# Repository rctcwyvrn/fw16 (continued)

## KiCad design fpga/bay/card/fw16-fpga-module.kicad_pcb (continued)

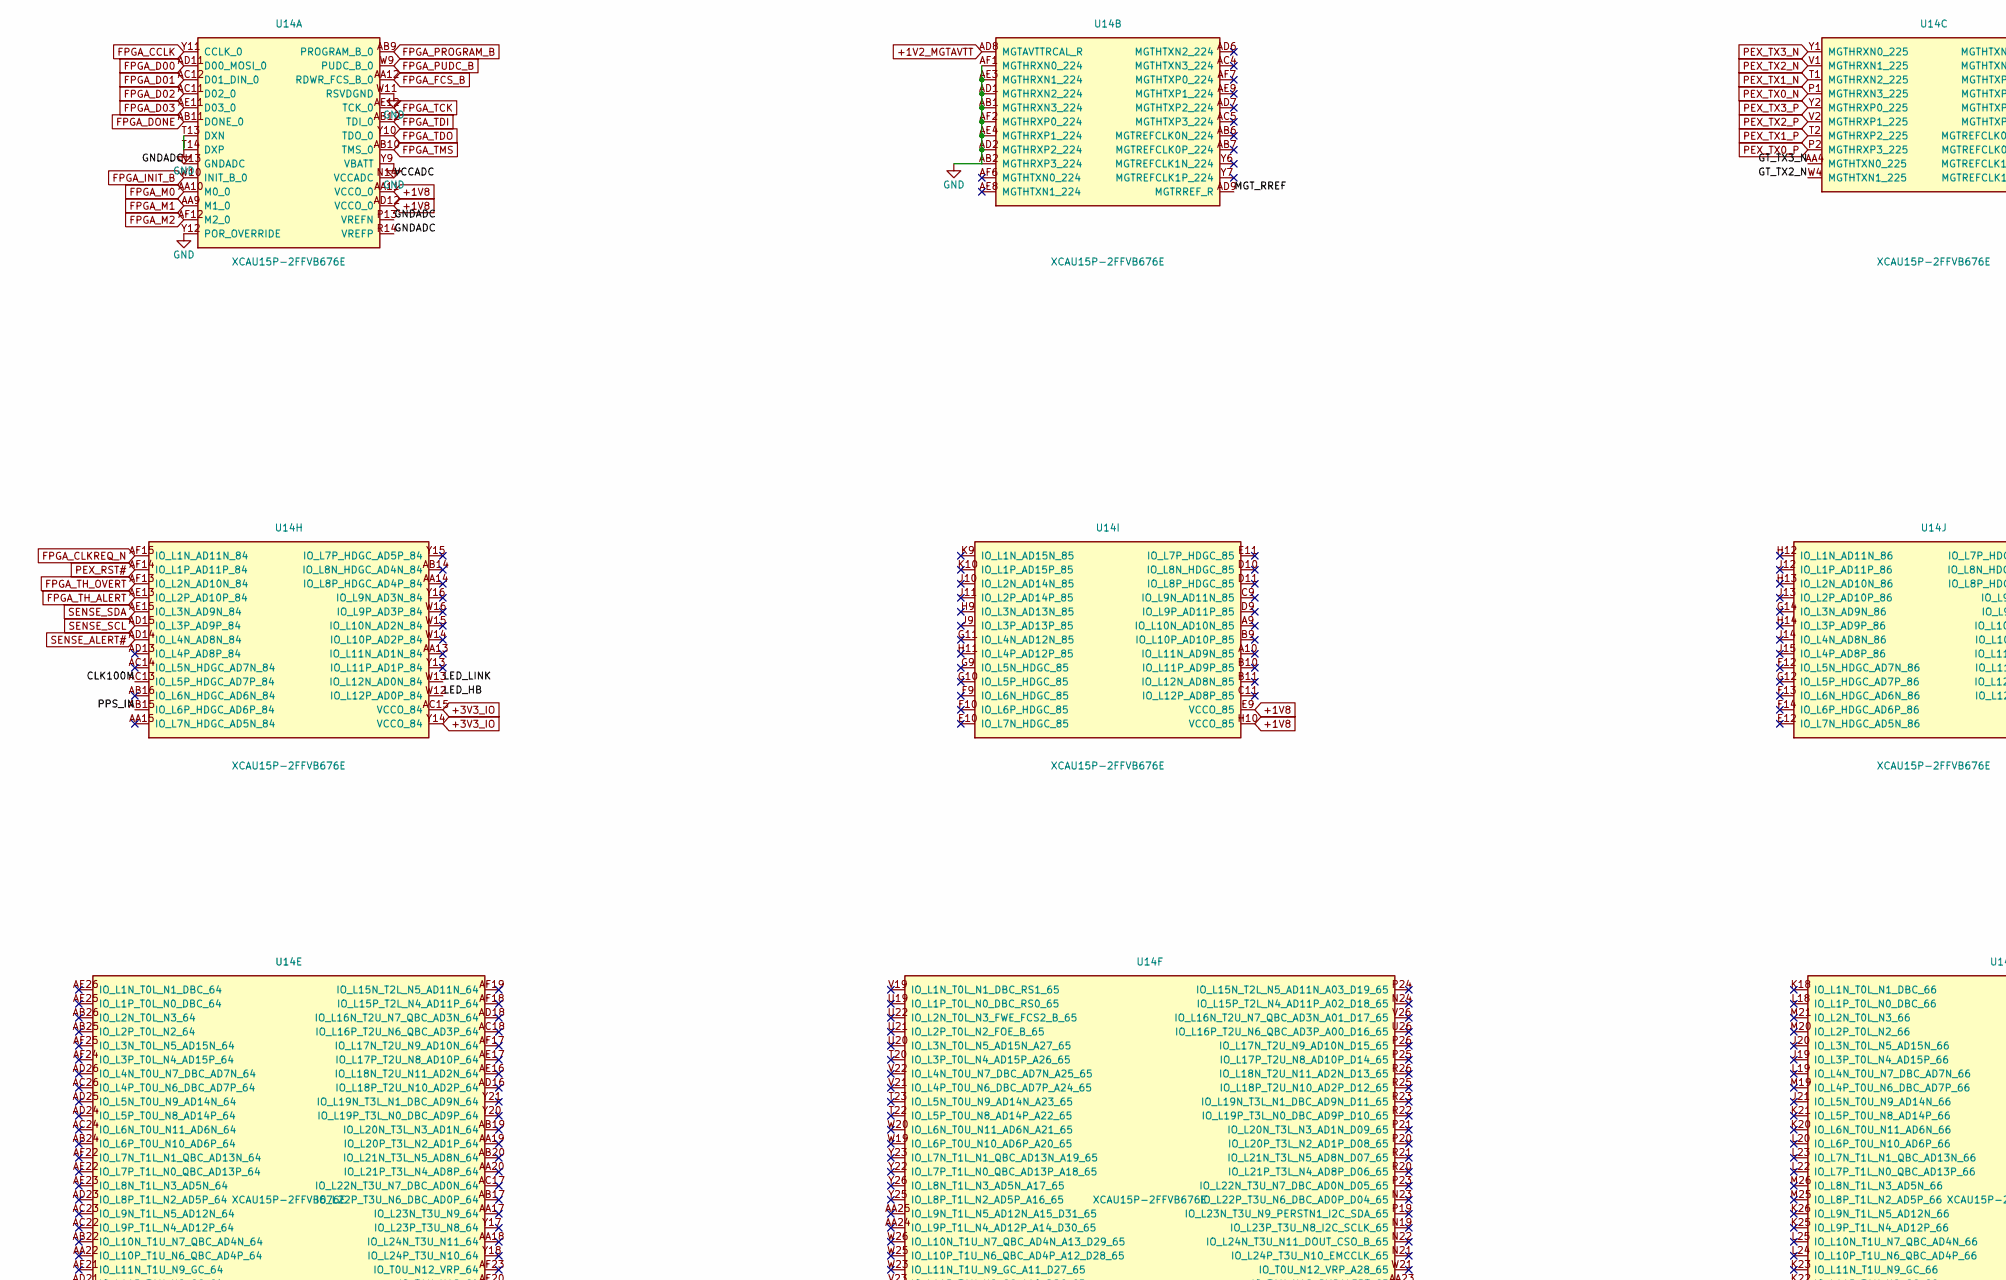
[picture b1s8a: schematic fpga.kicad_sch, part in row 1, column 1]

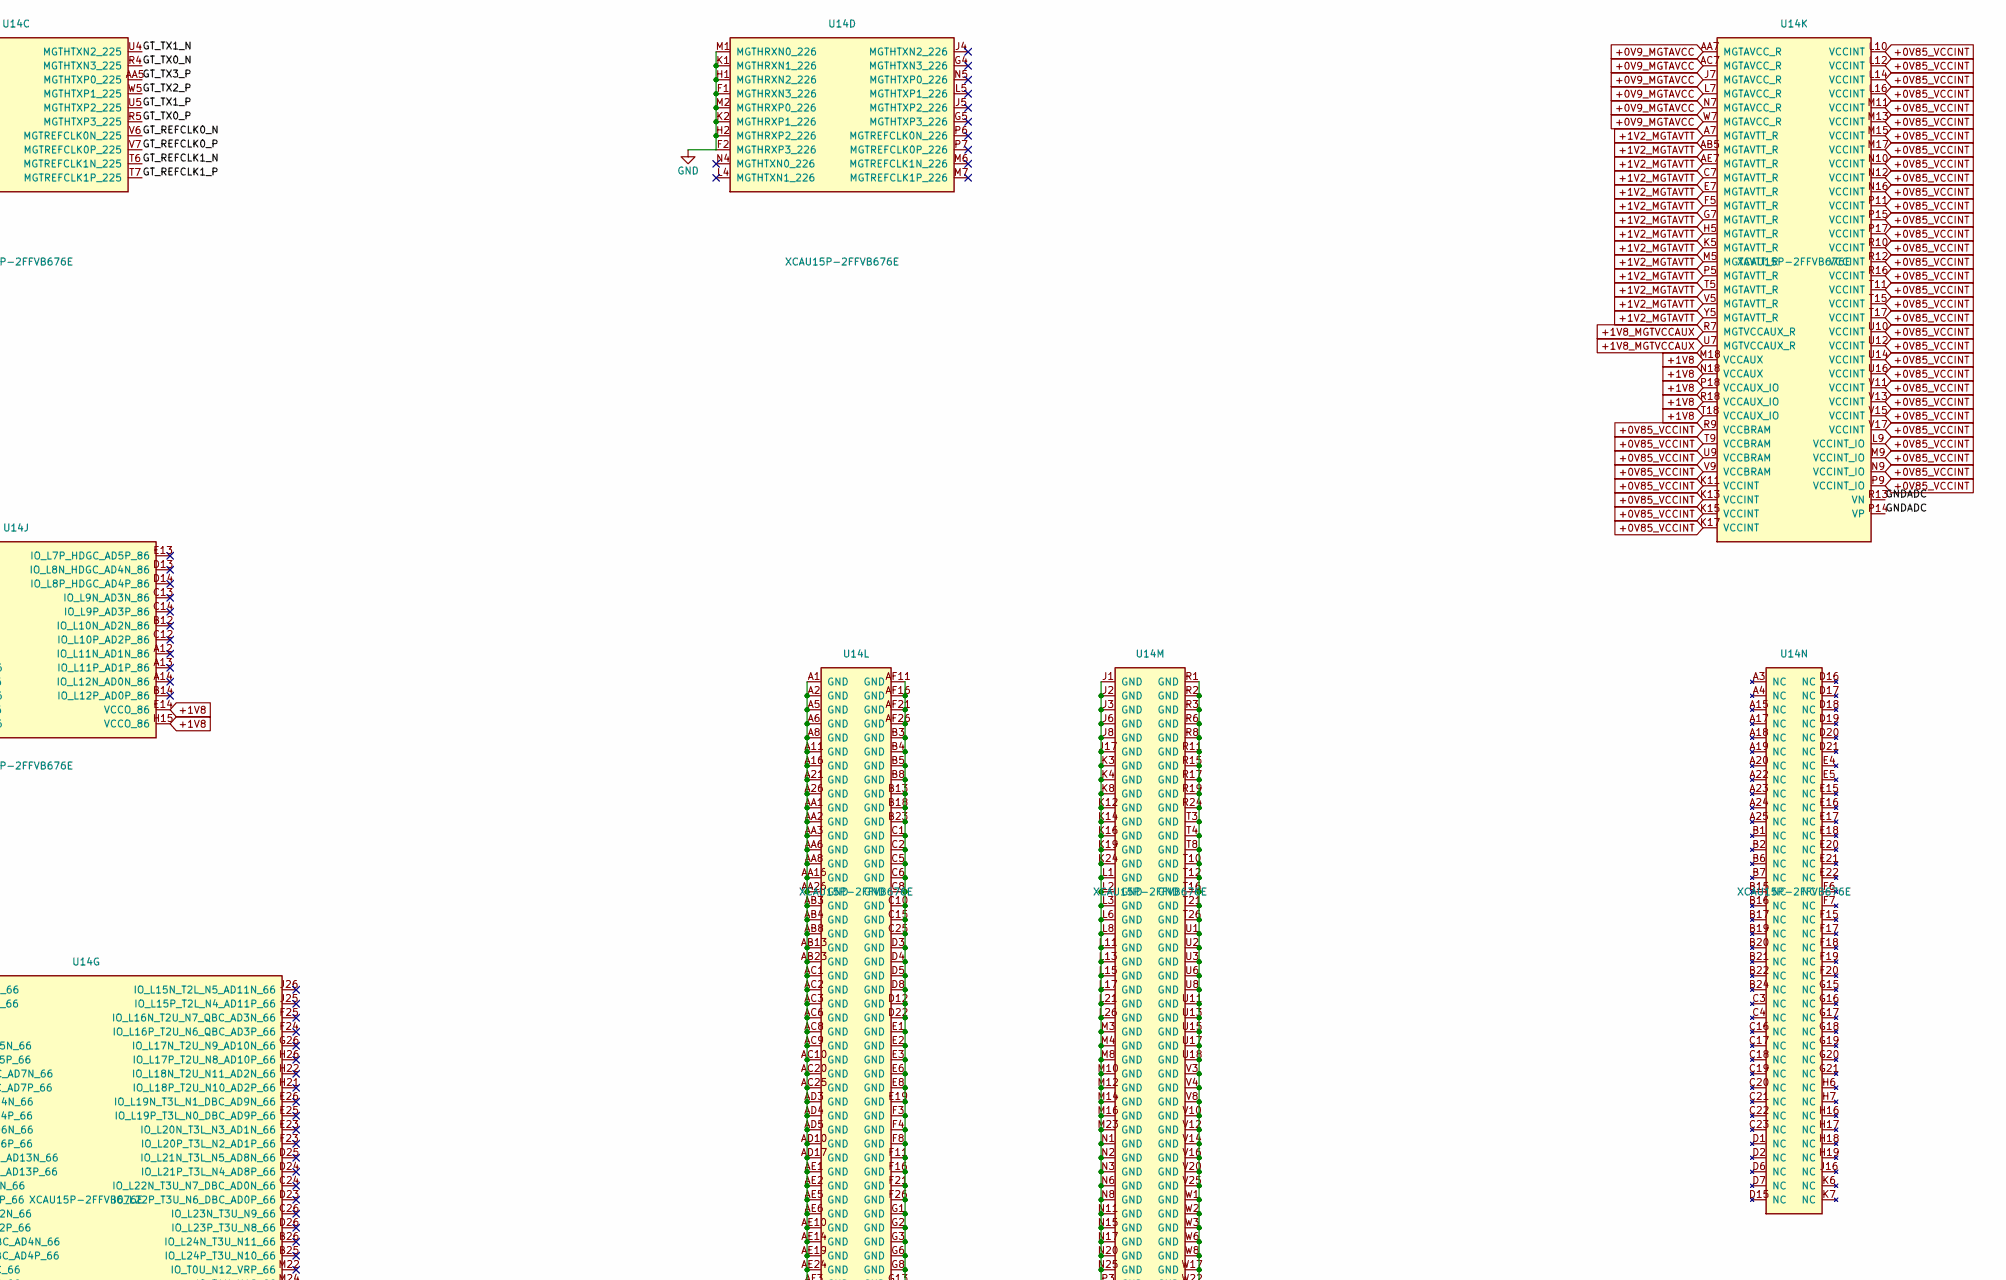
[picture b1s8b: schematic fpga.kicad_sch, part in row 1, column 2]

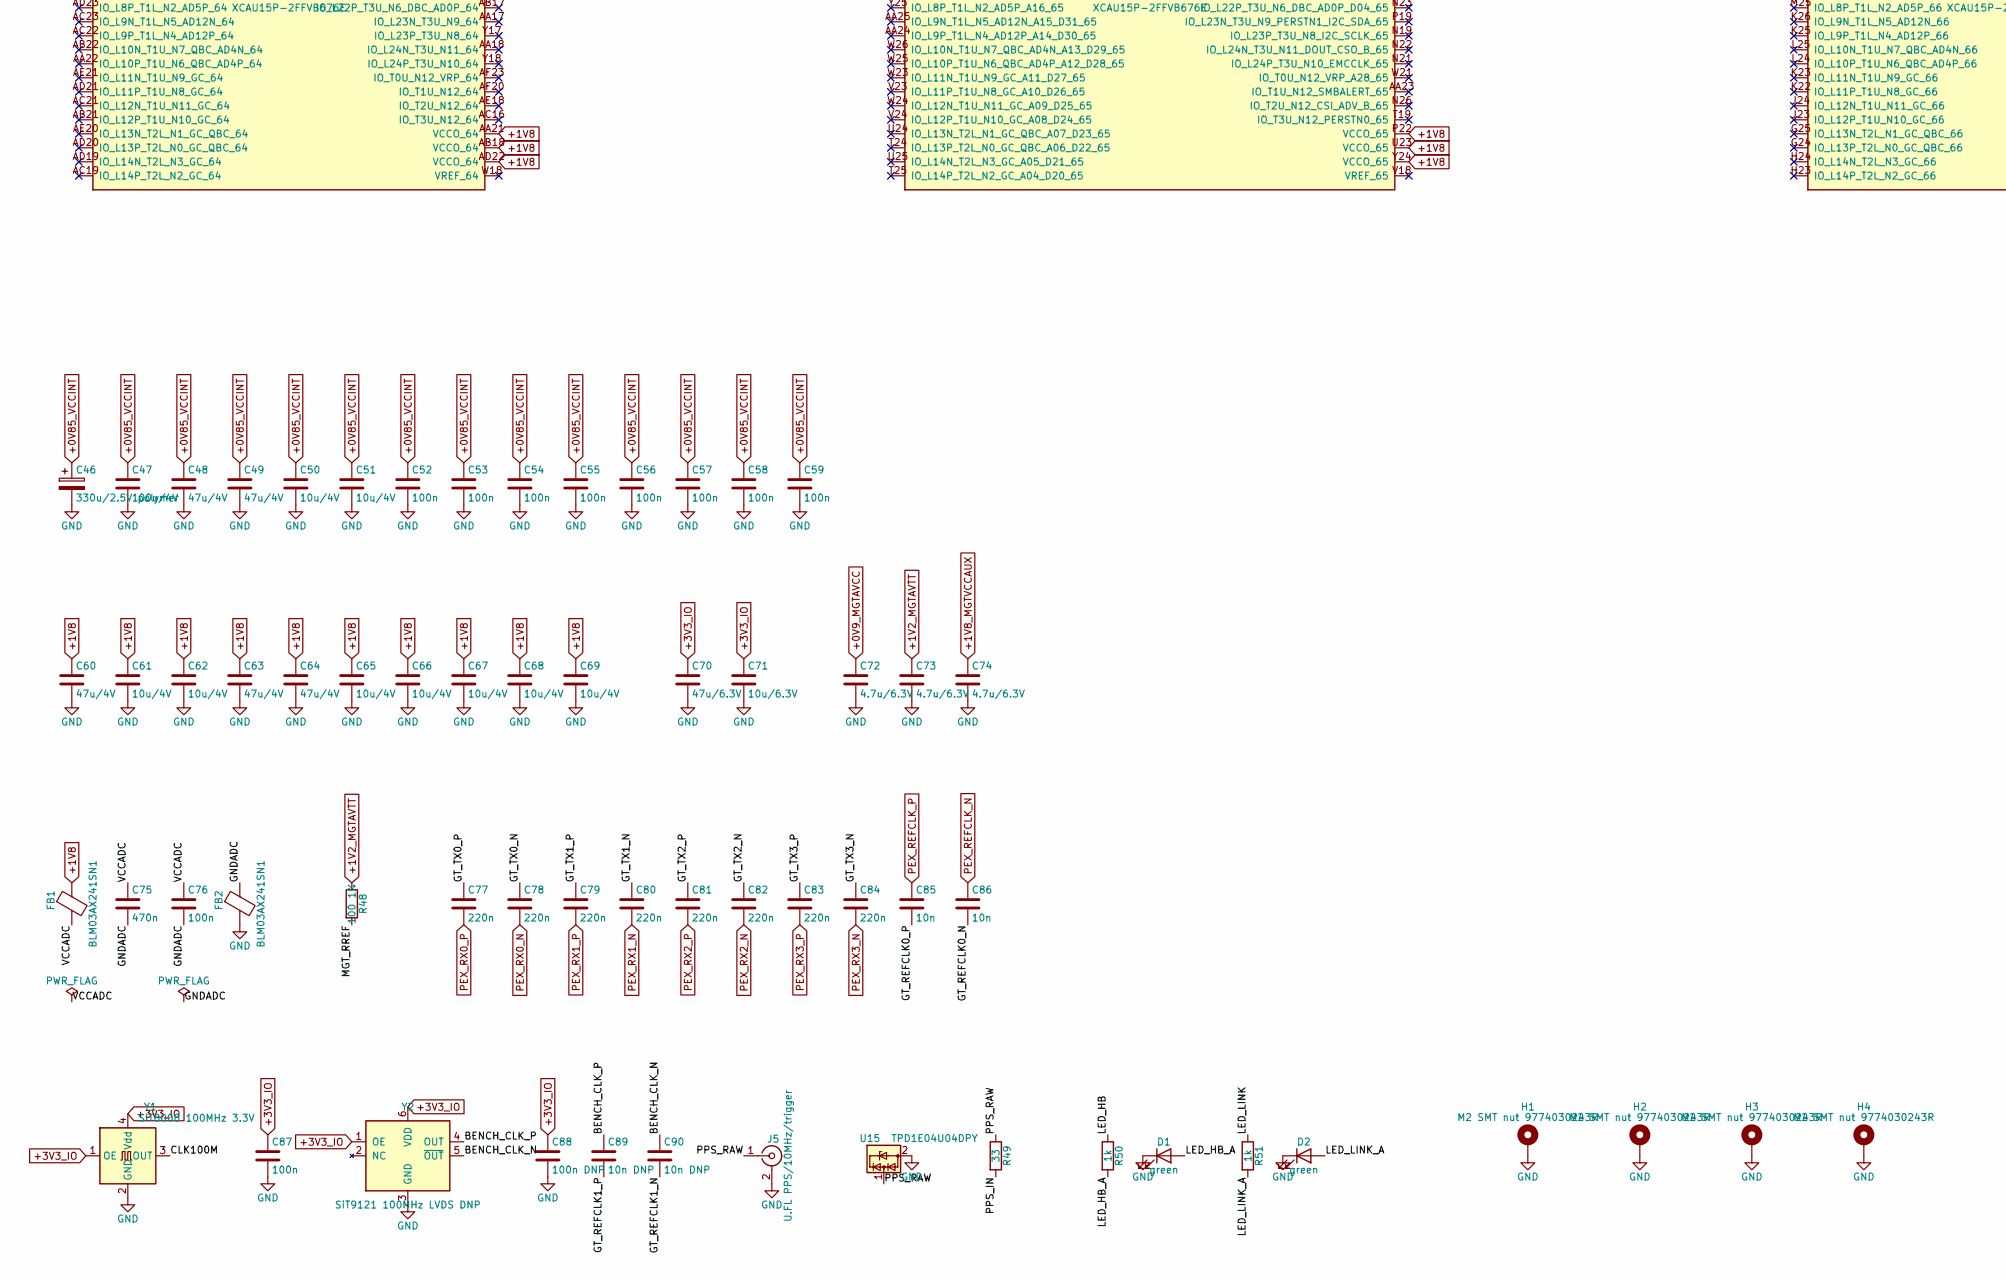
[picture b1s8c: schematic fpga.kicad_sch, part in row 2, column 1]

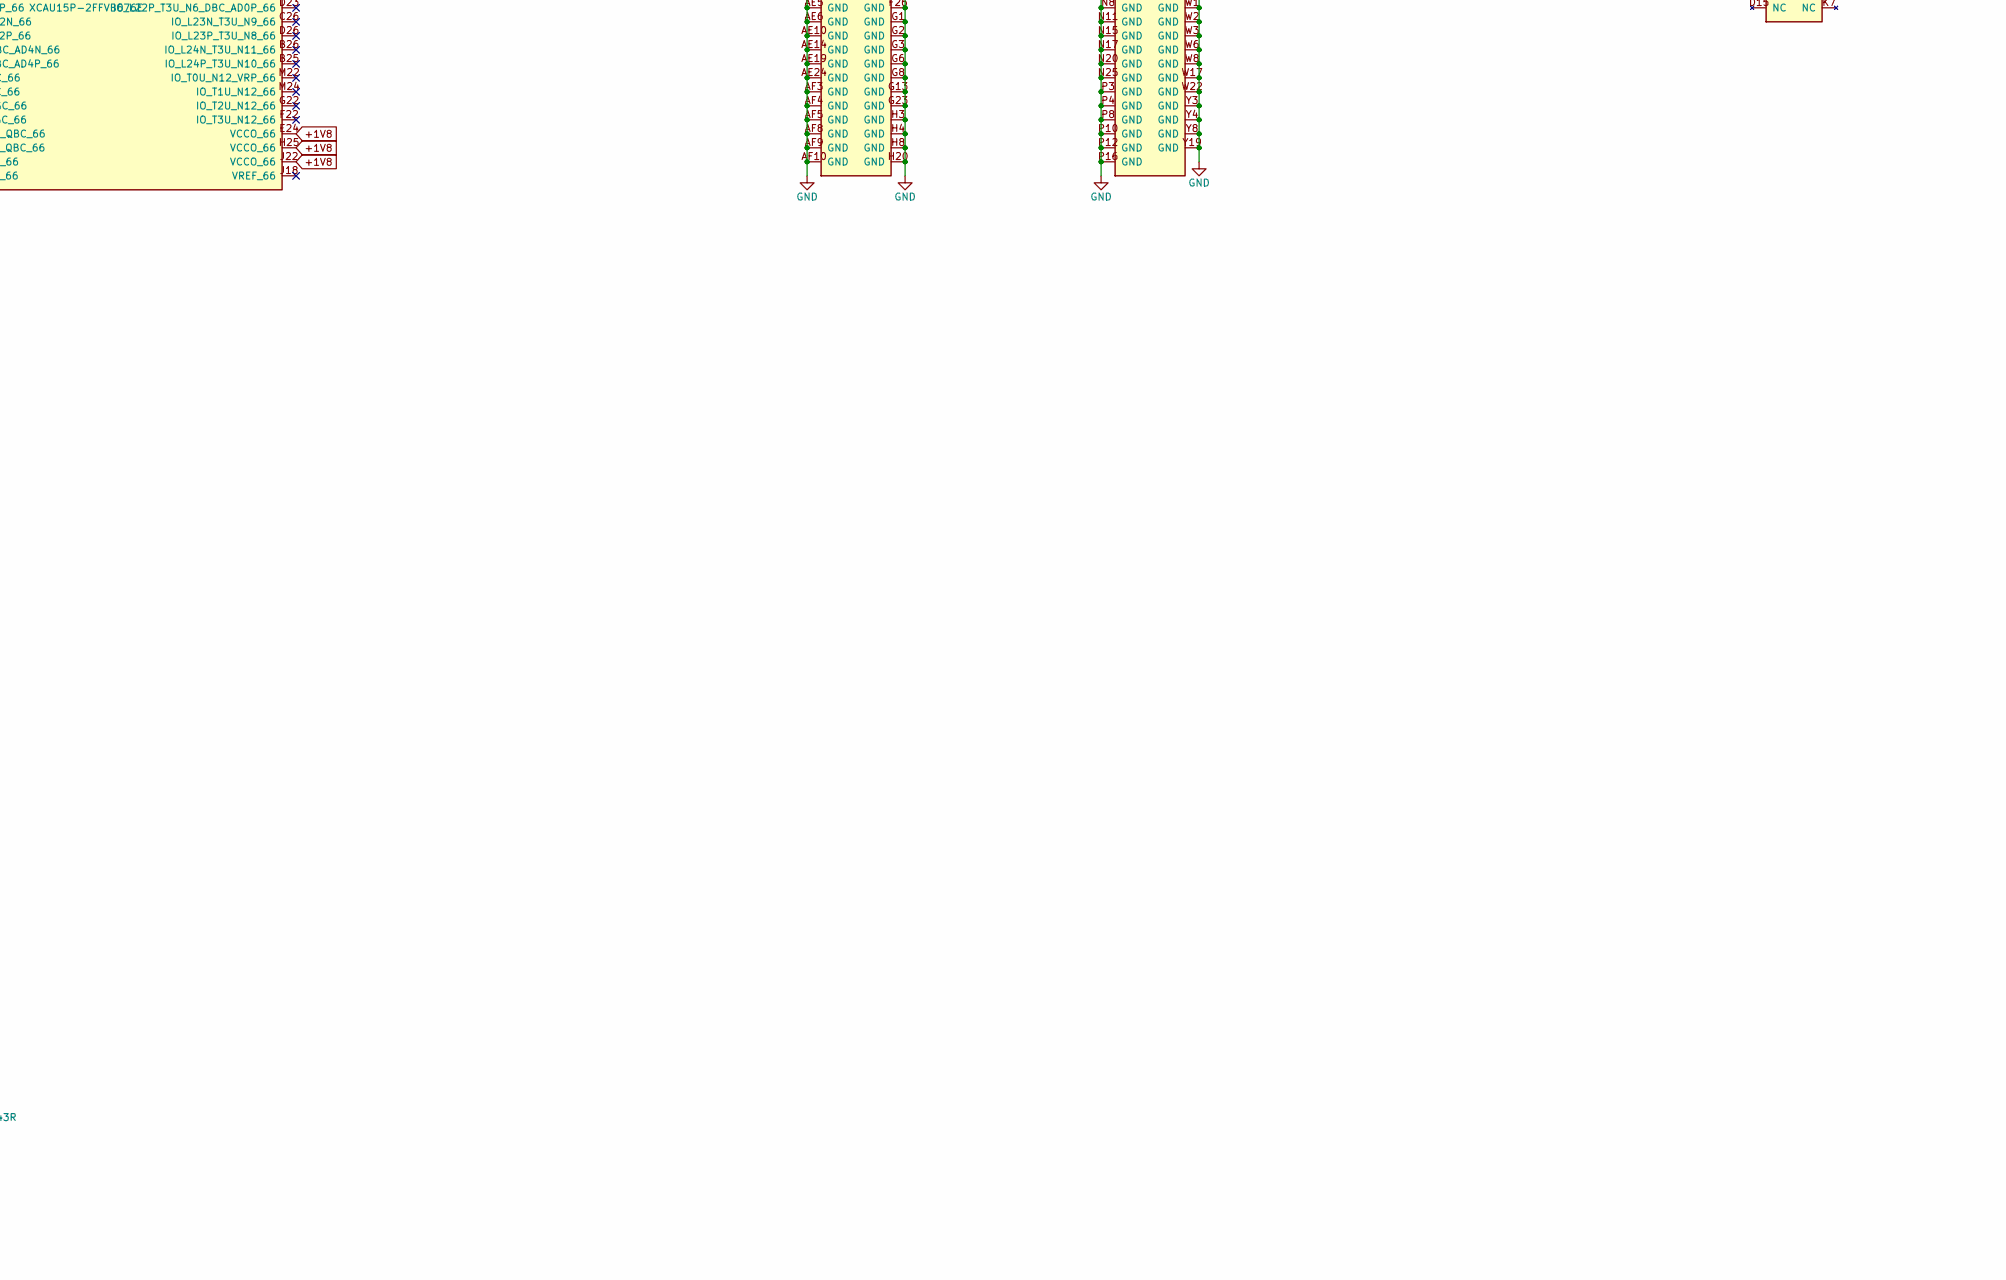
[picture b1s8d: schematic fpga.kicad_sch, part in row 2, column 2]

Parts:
C46: 330u/2.5V polymer; CP_EIA-7343-31_Kemet-D
C47: 100u/4V; C_1210_3225Metric
C48, C49, C60, C63, C64: 47u/4V; C_1206_3216Metric
C50, C51, C61, C62, C65, C66, C67, C68, C69: 10u/4V; C_0603_1608Metric
C52, C53, C54, C55, C56, C57, C58, C59, C76: 100n; C_0201_0603Metric
C70: 47u/6.3V; C_1206_3216Metric
C71: 10u/6.3V; C_0603_1608Metric
C72, C73, C74: 4.7u/6.3V; C_0603_1608Metric
C75: 470n; C_0201_0603Metric
C77, C78, C79, C80, C81, C82, C83, C84: 220n; C_0402_1005Metric
C85, C86: 10n; C_0402_1005Metric
C87: 100n; C_0402_1005Metric
C88: 100n DNP; C_0402_1005Metric
C89, C90: 10n DNP; C_0402_1005Metric
D1, D2: green; LED_0603_1608Metric
FB1, FB2: BLM03AX241SN1; L_0201_0603Metric
H1, H2, H3, H4: M2 SMT nut 9774030243R; Wurth_WA-SMSI_M2_9774030243R
J5: U.FL PPS/10MHz/trigger; U.FL_Hirose_U.FL-R-SMT-1_Vertical
R48: 100 1%; R_0402_1005Metric
R49: 33; R_0402_1005Metric
R50, R51: 1k; R_0402_1005Metric
U14: XCAU15P-2FFVB676E; BGA-676_27.0x27.0mm_Layout26x26_P1.0mm_Ball0.6mm_Pad0.5mm_N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
U15: TPD1E04U04DPY; Texas_DPY0002A_0.6x1mm_P0.65mm
Y1: SiT8008 100MHz 3.3V; Oscillator_SMD_SiT_PQFN-4Pin_2.0x1.6mm
Y2: SiT9121 100MHz LVDS DNP; Oscillator_SMD_SiTime_SiT9121-6Pin_3.2x2.5mm

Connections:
+0V9_MGTAVCC: C72.1, U14.AA7 (MGTAVCC_R), U14.AC7 (MGTAVCC_R), U14.J7 (MGTAVCC_R), U14.L7 (MGTAVCC_R), U14.N7 (MGTAVCC_R), U14.W7 (MGTAVCC_R); also elsewhere on the board
+0V85_VCCINT: C46.1, C47.1, C48.1, C49.1, C50.1, C51.1, C52.1, C53.1, C54.1, C55.1, C56.1, C57.1, C58.1, C59.1, U14.K11 (VCCINT), U14.K13 (VCCINT), U14.K15 (VCCINT), U14.K17 (VCCINT), U14.L9 (VCCINT_IO), U14.L10 (VCCINT), U14.L12 (VCCINT), U14.L14 (VCCINT), U14.L16 (VCCINT), U14.M9 (VCCINT_IO), U14.M11 (VCCINT), U14.M13 (VCCINT), U14.M15 (VCCINT), U14.M17 (VCCINT), U14.N9 (VCCINT_IO), U14.N10 (VCCINT), U14.N12 (VCCINT), U14.N16 (VCCINT), U14.P9 (VCCINT_IO), U14.P11 (VCCINT), U14.P15 (VCCINT), U14.P17 (VCCINT), U14.R9 (VCCBRAM), U14.R10 (VCCINT), U14.R12 (VCCINT), U14.R16 (VCCINT), U14.T9 (VCCBRAM), U14.T11 (VCCINT), U14.T15 (VCCINT), U14.T17 (VCCINT), U14.U9 (VCCBRAM), U14.U10 (VCCINT), U14.U12 (VCCINT), U14.U14 (VCCINT), U14.U16 (VCCINT), U14.V9 (VCCBRAM), U14.V11 (VCCINT), U14.V13 (VCCINT), U14.V15 (VCCINT), U14.V17 (VCCINT); also elsewhere on the board
+1V2_MGTAVTT: C73.1, R48.1, U14.A7 (MGTAVTT_R), U14.AB5 (MGTAVTT_R), U14.AD8 (MGTAVTTRCAL_R), U14.AE7 (MGTAVTT_R), U14.C7 (MGTAVTT_R), U14.E7 (MGTAVTT_R), U14.F5 (MGTAVTT_R), U14.G7 (MGTAVTT_R), U14.H5 (MGTAVTT_R), U14.K5 (MGTAVTT_R), U14.M5 (MGTAVTT_R), U14.P5 (MGTAVTT_R), U14.T5 (MGTAVTT_R), U14.V5 (MGTAVTT_R), U14.Y5 (MGTAVTT_R); also elsewhere on the board
+1V8: C60.1, C61.1, C62.1, C63.1, C64.1, C65.1, C66.1, C67.1, C68.1, C69.1, FB1.1, U14.AA11 (VCCO_0), U14.AA21 (VCCO_64), U14.AB18 (VCCO_64), U14.AD12 (VCCO_0), U14.AD22 (VCCO_64), U14.E9 (VCCO_85), U14.E14 (VCCO_86), U14.E24 (VCCO_66), U14.H10 (VCCO_85), U14.H15 (VCCO_86), U14.H25 (VCCO_66), U14.J22 (VCCO_66), U14.M18 (VCCAUX), U14.N18 (VCCAUX), U14.P18 (VCCAUX_IO), U14.P22 (VCCO_65), U14.R18 (VCCAUX_IO), U14.T18 (VCCAUX_IO), U14.U23 (VCCO_65), U14.Y24 (VCCO_65); also elsewhere on the board
+1V8_MGTVCCAUX: C74.1, U14.R7 (MGTVCCAUX_R), U14.U7 (MGTVCCAUX_R); also elsewhere on the board
+3V3_IO: C70.1, C71.1, C87.1, C88.1, U14.AC15 (VCCO_84), U14.Y14 (VCCO_84), Y1.1 (OE), Y1.4 (Vdd), Y2.1 (OE), Y2.6 (VDD); also elsewhere on the board
/FPGA/BENCH_CLK_N: C90.1, Y2.5 (~OUT)
/FPGA/BENCH_CLK_P: C89.1, Y2.4 (OUT)
/FPGA/CLK100M: U14.AC13 (IO_L5P_HDGC_AD7P_84), Y1.3 (OUT)
/FPGA/GNDADC: C75.2, C76.2, FB2.1, U14.N13 (GNDADC), U14.P13 (VREFN), U14.P14 (VP), U14.R13 (VN), U14.R14 (VREFP)
/FPGA/GT_REFCLK0_N: C86.2, U14.V6 (MGTREFCLK0N_225)
/FPGA/GT_REFCLK0_P: C85.2, U14.V7 (MGTREFCLK0P_225)
/FPGA/GT_REFCLK1_N: C90.2, U14.T6 (MGTREFCLK1N_225)
/FPGA/GT_REFCLK1_P: C89.2, U14.T7 (MGTREFCLK1P_225)
/FPGA/GT_TX0_N: C78.1, U14.R4 (MGTHTXN3_225)
/FPGA/GT_TX0_P: C77.1, U14.R5 (MGTHTXP3_225)
/FPGA/GT_TX1_N: C80.1, U14.U4 (MGTHTXN2_225)
/FPGA/GT_TX1_P: C79.1, U14.U5 (MGTHTXP2_225)
/FPGA/GT_TX2_N: C82.1, U14.W4 (MGTHTXN1_225)
/FPGA/GT_TX2_P: C81.1, U14.W5 (MGTHTXP1_225)
/FPGA/GT_TX3_N: C84.1, U14.AA4 (MGTHTXN0_225)
/FPGA/GT_TX3_P: C83.1, U14.AA5 (MGTHTXP0_225)
/FPGA/LED_HB: R50.1, U14.W12 (IO_L12P_AD0P_84)
/FPGA/LED_HB_A: D1.2 (A), R50.2
/FPGA/LED_LINK: R51.1, U14.W13 (IO_L12N_AD0N_84)
/FPGA/LED_LINK_A: D2.2 (A), R51.2
/FPGA/MGT_RREF: R48.2, U14.AD9 (MGTRREF_R)
/FPGA/PPS_IN: R49.2, U14.AB15 (IO_L6P_HDGC_AD6P_84)
/FPGA/PPS_RAW: J5.1 (In), R49.1, U15.1 (I/O)
/FPGA/VCCADC: C75.1, C76.1, FB1.2, U14.N14 (VCCADC)
FPGA_CCLK: U14.Y11 (CCLK_0); also elsewhere on the board
FPGA_CLKREQ_N: U14.AF15 (IO_L1N_AD11N_84); also elsewhere on the board
FPGA_D00: U14.AD11 (D00_MOSI_0); also elsewhere on the board
FPGA_D01: U14.AC12 (D01_DIN_0); also elsewhere on the board
FPGA_D02: U14.AC11 (D02_0); also elsewhere on the board
FPGA_D03: U14.AE11 (D03_0); also elsewhere on the board
FPGA_DONE: U14.AB11 (DONE_0); also elsewhere on the board
FPGA_FCS_B: U14.AA12 (RDWR_FCS_B_0); also elsewhere on the board
FPGA_INIT_B: U14.W10 (INIT_B_0); also elsewhere on the board
FPGA_M0: U14.AA10 (M0_0); also elsewhere on the board
FPGA_M1: U14.AA9 (M1_0); also elsewhere on the board
FPGA_M2: U14.AF12 (M2_0); also elsewhere on the board
FPGA_PROGRAM_B: U14.AB9 (PROGRAM_B_0); also elsewhere on the board
FPGA_PUDC_B: U14.W9 (PUDC_B_0); also elsewhere on the board
FPGA_TCK: U14.AE12 (TCK_0); also elsewhere on the board
FPGA_TDI: U14.AB12 (TDI_0); also elsewhere on the board
FPGA_TDO: U14.Y10 (TDO_0); also elsewhere on the board
FPGA_TH_ALERT: U14.AE13 (IO_L2P_AD10P_84); also elsewhere on the board
FPGA_TH_OVERT: U14.AF13 (IO_L2N_AD10N_84); also elsewhere on the board
FPGA_TMS: U14.AB10 (TMS_0); also elsewhere on the board
GND: C46.2, C47.2, C48.2, C49.2, C50.2, C51.2, C52.2, C53.2, C54.2, C55.2, C56.2, C57.2, C58.2, C59.2, C60.2, C61.2, C62.2, C63.2, C64.2, C65.2, C66.2, C67.2, C68.2, C69.2, C70.2, C71.2, C72.2, C73.2, C74.2, C87.2, C88.2, D1.1 (K), D2.1 (K), FB2.2, H1.1, H2.1, H3.1, H4.1, J5.2 (Ext), U14.A1 (GND), U14.A2 (GND), U14.A5 (GND), U14.A6 (GND), U14.A8 (GND), U14.A11 (GND), U14.A16 (GND), U14.A21 (GND), U14.A26 (GND), U14.AA1 (GND), U14.AA2 (GND), U14.AA3 (GND), U14.AA6 (GND), U14.AA8 (GND), U14.AA16 (GND), U14.AA26 (GND), U14.AB1 (MGTHRXN3_224), U14.AB2 (MGTHRXP3_224), U14.AB3 (GND), U14.AB4 (GND), U14.AB8 (GND), U14.AB13 (GND), U14.AB23 (GND), U14.AC1 (GND), U14.AC2 (GND), U14.AC3 (GND), U14.AC6 (GND), U14.AC8 (GND), U14.AC9 (GND), U14.AC10 (GND), U14.AC20 (GND), U14.AC25 (GND), U14.AD1 (MGTHRXN2_224), U14.AD2 (MGTHRXP2_224), U14.AD3 (GND), U14.AD4 (GND), U14.AD5 (GND), U14.AD10 (GND), U14.AD17 (GND), U14.AE1 (GND), U14.AE2 (GND), U14.AE3 (MGTHRXN1_224), U14.AE4 (MGTHRXP1_224), U14.AE5 (GND), U14.AE6 (GND), U14.AE10 (GND), U14.AE14 (GND), U14.AE19 (GND), U14.AE24 (GND), U14.AF1 (MGTHRXN0_224), U14.AF2 (MGTHRXP0_224), U14.AF3 (GND), U14.AF4 (GND), U14.AF5 (GND), U14.AF8 (GND), U14.AF9 (GND), U14.AF10 (GND), U14.AF11 (GND), U14.AF16 (GND), U14.AF21 (GND), U14.AF26 (GND), U14.B3 (GND), U14.B4 (GND), U14.B5 (GND), U14.B8 (GND), U14.B13 (GND), U14.B18 (GND), U14.B23 (GND), U14.C1 (GND), U14.C2 (GND), U14.C5 (GND), U14.C6 (GND), U14.C8 (GND), U14.C10 (GND), U14.C15 (GND), U14.C25 (GND), U14.D3 (GND), U14.D4 (GND), U14.D5 (GND), U14.D8 (GND), U14.D12 (GND), U14.D22 (GND), U14.E1 (GND), U14.E2 (GND), U14.E3 (GND), U14.E6 (GND), U14.E8 (GND), U14.E19 (GND), U14.F1 (MGTHRXN3_226), U14.F2 (MGTHRXP3_226), U14.F3 (GND), U14.F4 (GND), U14.F8 (GND), U14.F11 (GND), U14.F16 (GND), U14.F21 (GND), U14.F26 (GND), U14.G1 (GND), U14.G2 (GND), U14.G3 (GND), U14.G6 (GND), U14.G8 (GND), U14.G13 (GND), U14.G23 (GND), U14.H1 (MGTHRXN2_226), U14.H2 (MGTHRXP2_226), U14.H3 (GND), U14.H4 (GND), U14.H8 (GND), U14.H20 (GND), U14.J1 (GND), U14.J2 (GND), U14.J3 (GND), U14.J6 (GND), U14.J8 (GND), U14.J17 (GND), U14.K1 (MGTHRXN1_226), U14.K2 (MGTHRXP1_226), U14.K3 (GND), U14.K4 (GND), U14.K8 (GND), U14.K12 (GND), U14.K14 (GND), U14.K16 (GND), U14.K19 (GND), U14.K24 (GND), U14.L1 (GND), U14.L2 (GND), U14.L3 (GND), U14.L6 (GND), U14.L8 (GND), U14.L11 (GND), U14.L13 (GND), U14.L15 (GND), U14.L17 (GND), U14.L21 (GND), U14.L26 (GND), U14.M1 (MGTHRXN0_226), U14.M2 (MGTHRXP0_226), U14.M3 (GND), U14.M4 (GND), U14.M8 (GND), U14.M10 (GND), U14.M12 (GND), U14.M14 (GND), U14.M16 (GND), U14.M23 (GND), U14.N1 (GND), U14.N2 (GND), U14.N3 (GND), U14.N6 (GND), U14.N8 (GND), U14.N11 (GND), U14.N15 (GND), U14.N17 (GND), U14.N20 (GND), U14.N25 (GND), U14.P3 (GND), U14.P4 (GND), U14.P8 (GND), U14.P10 (GND), U14.P12 (GND), U14.P16 (GND), U14.R1 (GND), U14.R2 (GND), U14.R3 (GND), U14.R6 (GND), U14.R8 (GND), U14.R11 (GND), U14.R15 (GND), U14.R17 (GND), U14.R19 (GND), U14.R24 (GND), U14.T3 (GND), U14.T4 (GND), U14.T8 (GND), U14.T10 (GND), U14.T12 (GND), U14.T13 (DXN), U14.T14 (DXP), U14.T16 (GND), U14.T21 (GND), U14.T26 (GND), U14.U1 (GND), U14.U2 (GND), U14.U3 (GND), U14.U6 (GND), U14.U8 (GND), U14.U11 (GND), U14.U13 (GND), U14.U15 (GND), U14.U17 (GND), U14.U18 (GND), U14.V3 (GND), U14.V4 (GND), U14.V8 (GND), U14.V10 (GND), U14.V12 (GND), U14.V14 (GND), U14.V16 (GND), U14.V20 (GND), U14.V25 (GND), U14.W1 (GND), U14.W2 (GND), U14.W3 (GND), U14.W6 (GND), U14.W8 (GND), U14.W11 (RSVDGND), U14.W17 (GND), U14.W22 (GND), U14.Y3 (GND), U14.Y4 (GND), U14.Y8 (GND), U14.Y9 (VBATT), U14.Y12 (POR_OVERRIDE), U14.Y19 (GND), U15.2 (GND), Y1.2 (GND), Y2.3 (GND); also elsewhere on the board
PEX_REFCLK_N: C86.1; also elsewhere on the board
PEX_REFCLK_P: C85.1; also elsewhere on the board
PEX_RST#: U14.AF14 (IO_L1P_AD11P_84); also elsewhere on the board
PEX_RX0_N: C78.2; also elsewhere on the board
PEX_RX0_P: C77.2; also elsewhere on the board
PEX_RX1_N: C80.2; also elsewhere on the board
PEX_RX1_P: C79.2; also elsewhere on the board
PEX_RX2_N: C82.2; also elsewhere on the board
PEX_RX2_P: C81.2; also elsewhere on the board
PEX_RX3_N: C84.2; also elsewhere on the board
PEX_RX3_P: C83.2; also elsewhere on the board
PEX_TX0_N: U14.P1 (MGTHRXN3_225); also elsewhere on the board
PEX_TX0_P: U14.P2 (MGTHRXP3_225); also elsewhere on the board
PEX_TX1_N: U14.T1 (MGTHRXN2_225); also elsewhere on the board
PEX_TX1_P: U14.T2 (MGTHRXP2_225); also elsewhere on the board
PEX_TX2_N: U14.V1 (MGTHRXN1_225); also elsewhere on the board
PEX_TX2_P: U14.V2 (MGTHRXP1_225); also elsewhere on the board
PEX_TX3_N: U14.Y1 (MGTHRXN0_225); also elsewhere on the board
PEX_TX3_P: U14.Y2 (MGTHRXP0_225); also elsewhere on the board
SENSE_ALERT#: U14.AD14 (IO_L4N_AD8N_84); also elsewhere on the board
SENSE_SCL: U14.AD15 (IO_L3P_AD9P_84); also elsewhere on the board
SENSE_SDA: U14.AE15 (IO_L3N_AD9N_84); also elsewhere on the board

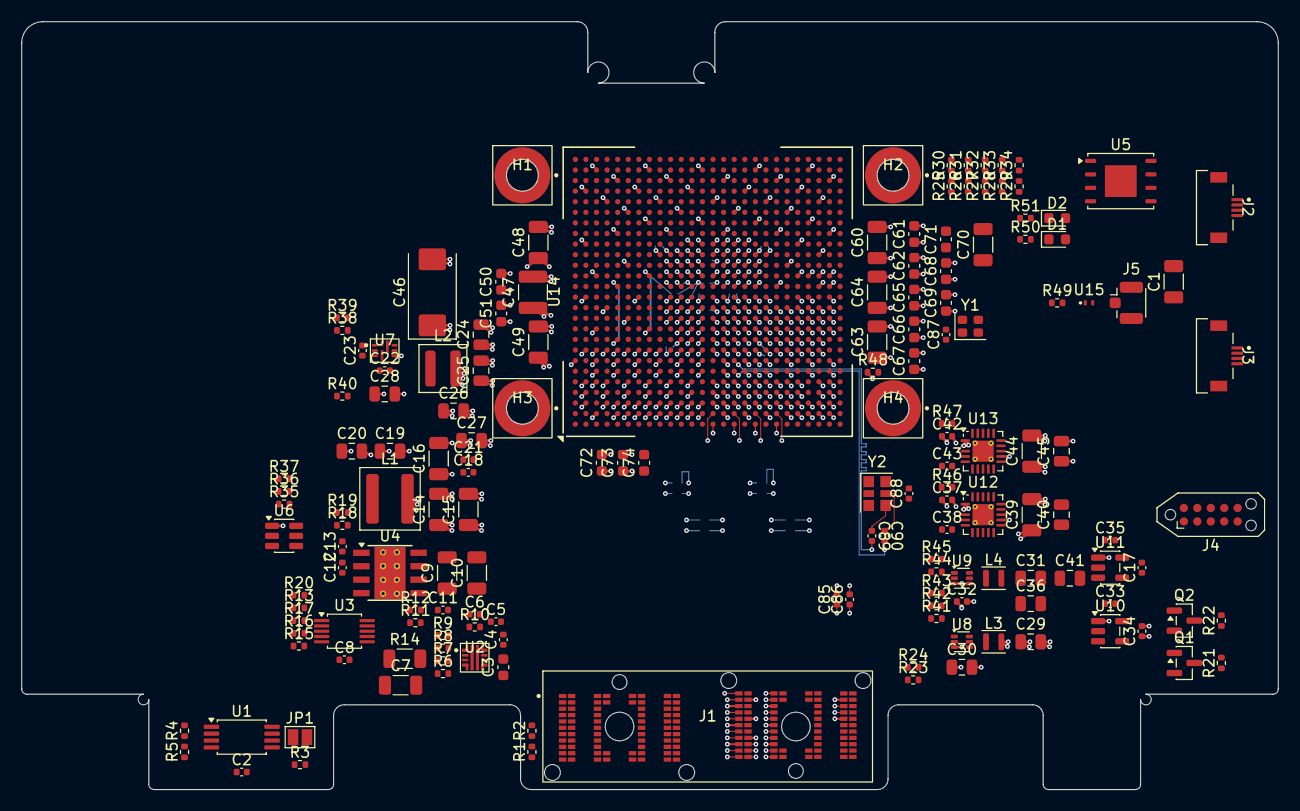
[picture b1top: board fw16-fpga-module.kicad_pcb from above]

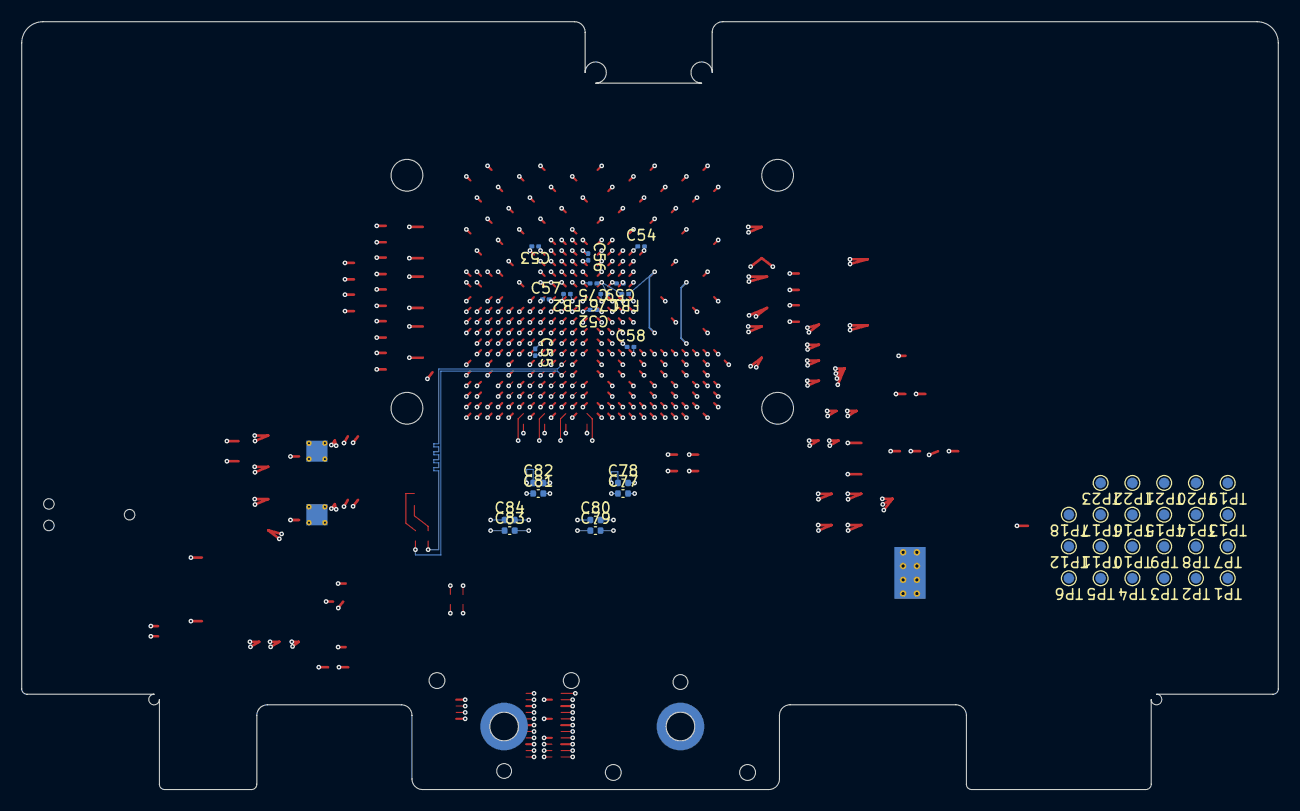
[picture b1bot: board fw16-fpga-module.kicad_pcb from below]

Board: 8 copper layers, 118.7 x 72.5 mm, 201 parts (43 on the bottom side), 136 nets.

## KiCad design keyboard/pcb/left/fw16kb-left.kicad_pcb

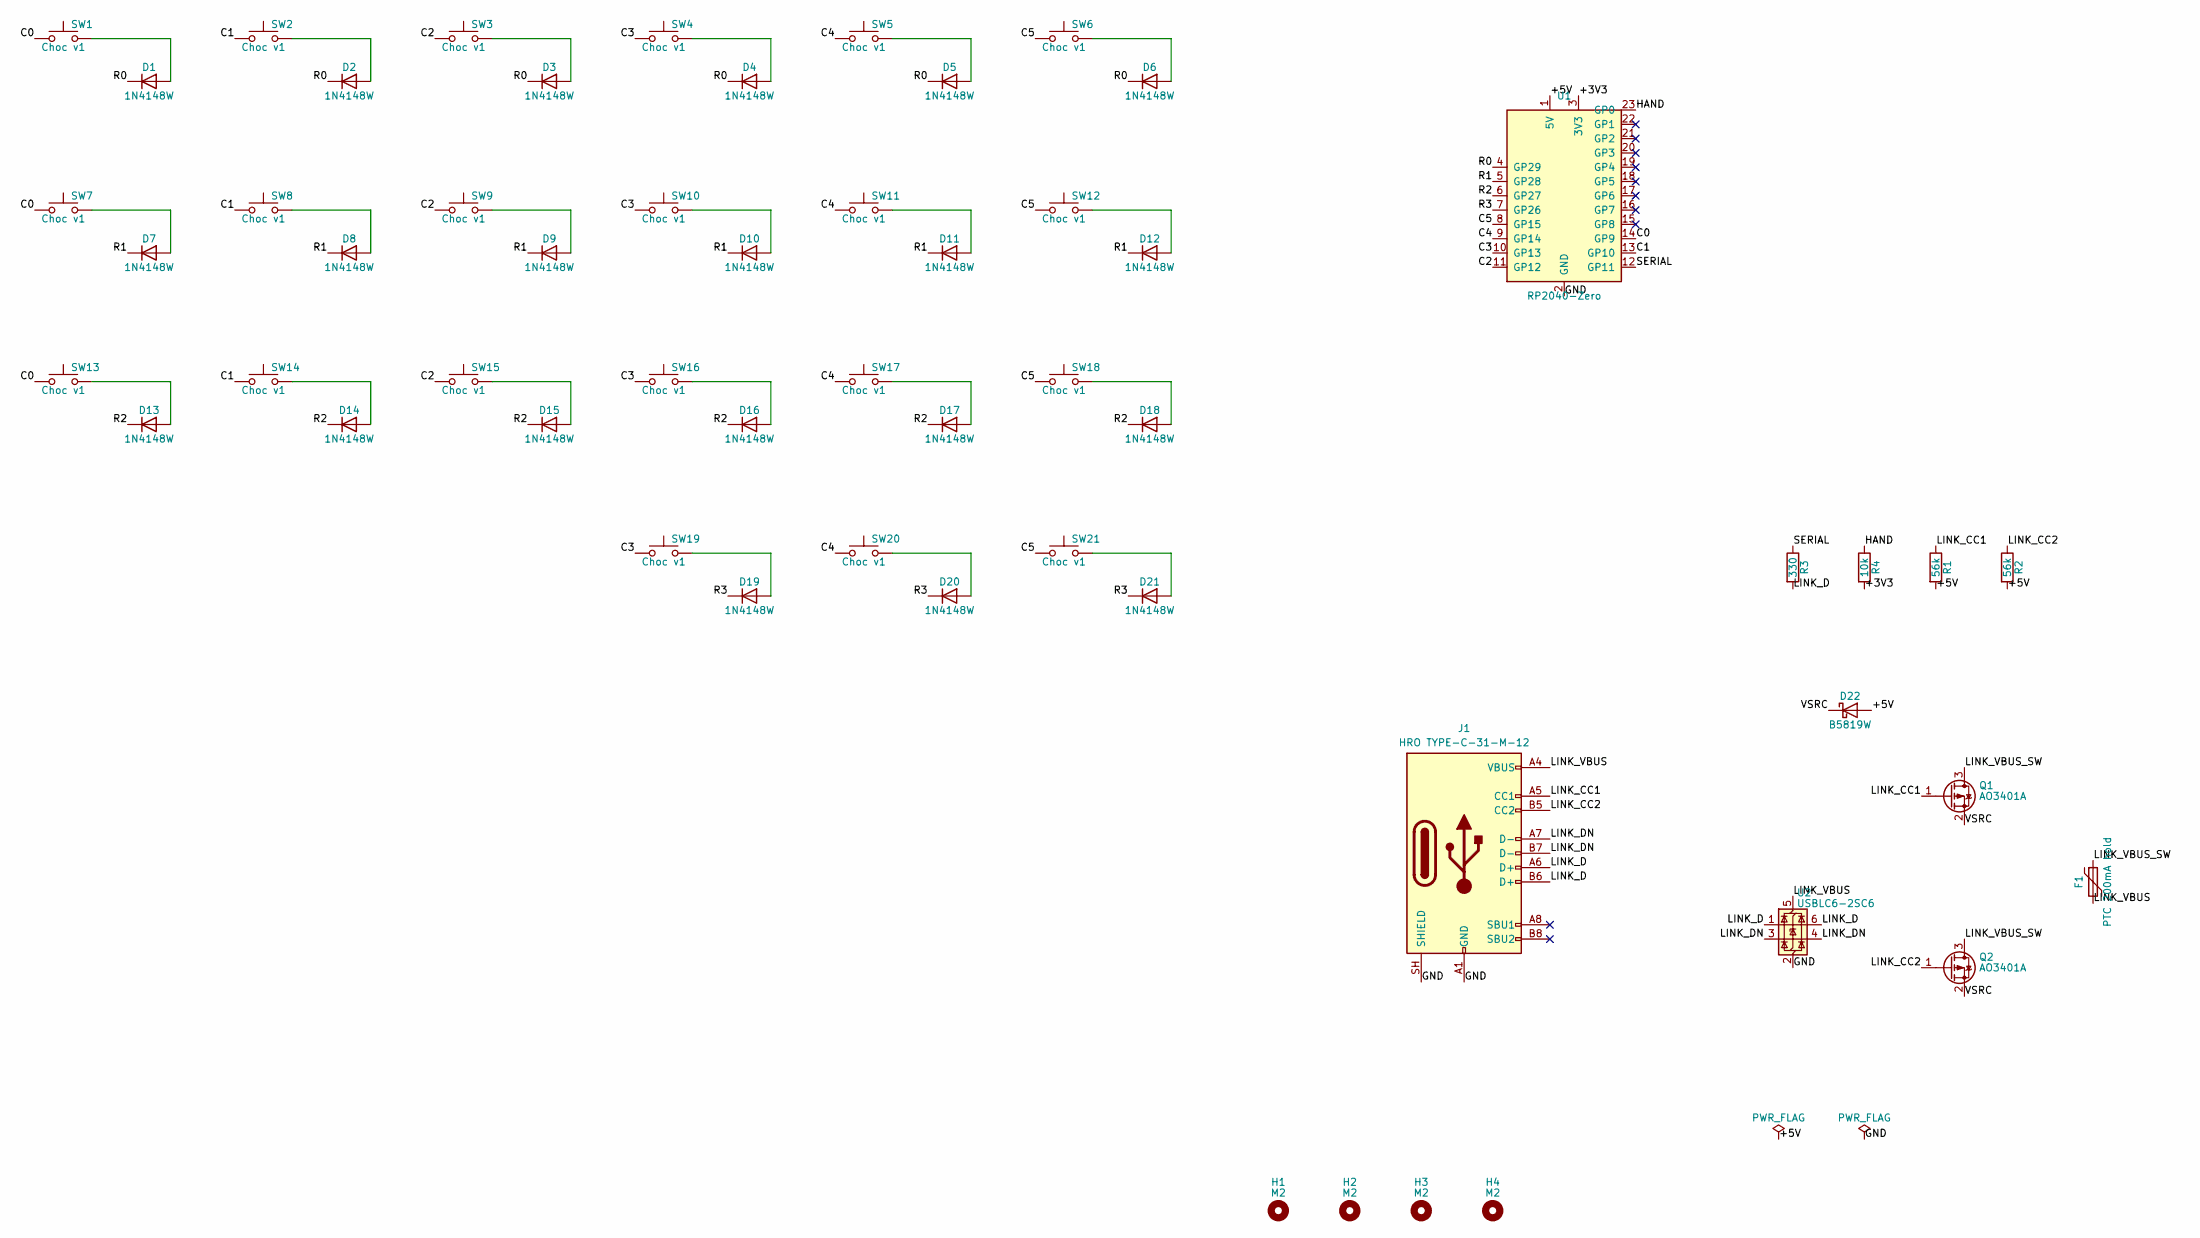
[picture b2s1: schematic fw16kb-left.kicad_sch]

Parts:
D1, D2, D3, D4, D5, D6, D7, D8, D9, D10, D11, D12, D13, D14, D15, D16, D17, D18, D19, D20, D21: 1N4148W; D_SOD-123
D22: B5819W; D_SOD-123
F1: PTC 200mA hold; Fuse_0805_2012Metric
H1, H2, H3, H4: M2; MountingHole_2.2mm_M2
J1: HRO TYPE-C-31-M-12; USB_C_Receptacle_HRO_TYPE-C-31-M-12
Q1, Q2: AO3401A; SOT-23
R1, R2: 56k; R_0805_2012Metric
R3: 330; R_0805_2012Metric
R4: 10k; R_0805_2012Metric
SW1, SW2, SW3, SW4, SW5, SW6, SW7, SW8, SW9, SW10, SW11, SW12, SW13, SW14, SW15, SW16, SW17, SW18, SW19, SW20, SW21: Choc v1; Choc_v1_Hotswap
U1: RP2040-Zero; RP2040-Zero_Castellated
U2: USBLC6-2SC6; SOT-23-6

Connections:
/+3V3: R4.2, U1.3 (3V3)
/+5V: D22.2 (A), R1.2, R2.2, U1.1 (5V)
/C0: SW1.1, SW7.1, SW13.1, U1.14 (GP9)
/C1: SW2.1, SW8.1, SW14.1, U1.13 (GP10)
/C2: SW3.1, SW9.1, SW15.1, U1.11 (GP12)
/C3: SW4.1, SW10.1, SW16.1, SW19.1, U1.10 (GP13)
/C4: SW5.1, SW11.1, SW17.1, SW20.1, U1.9 (GP14)
/C5: SW6.1, SW12.1, SW18.1, SW21.1, U1.8 (GP15)
/GND: J1.A1 (GND), J1.A12 (GND), J1.B1 (GND), J1.B12 (GND), J1.SH (SHIELD), U1.2 (GND), U2.2 (GND)
/HAND: R4.1, U1.23 (GP0)
/LINK_CC1: J1.A5 (CC1), Q1.1 (G), R1.1
/LINK_CC2: J1.B5 (CC2), Q2.1 (G), R2.1
/LINK_D: J1.A6 (D+), J1.B6 (D+), R3.2, U2.1 (I/O1), U2.6 (I/O1)
/LINK_DN: J1.A7 (D-), J1.B7 (D-), U2.3 (I/O2), U2.4 (I/O2)
/LINK_VBUS: F1.2, J1.A4 (VBUS), J1.A9 (VBUS), J1.B4 (VBUS), J1.B9 (VBUS), U2.5 (VBUS)
/LINK_VBUS_SW: F1.1, Q1.3 (D), Q2.3 (D)
/R0: D1.1 (K), D2.1 (K), D3.1 (K), D4.1 (K), D5.1 (K), D6.1 (K), U1.4 (GP29)
/R1: D7.1 (K), D8.1 (K), D9.1 (K), D10.1 (K), D11.1 (K), D12.1 (K), U1.5 (GP28)
/R2: D13.1 (K), D14.1 (K), D15.1 (K), D16.1 (K), D17.1 (K), D18.1 (K), U1.6 (GP27)
/R3: D19.1 (K), D20.1 (K), D21.1 (K), U1.7 (GP26)
/SERIAL: R3.1, U1.12 (GP11)
/VSRC: D22.1 (K), Q1.2 (S), Q2.2 (S)
unnamed: D1.2 (A), SW1.2
unnamed: D2.2 (A), SW2.2
unnamed: D3.2 (A), SW3.2
unnamed: D4.2 (A), SW4.2
unnamed: D5.2 (A), SW5.2
unnamed: D6.2 (A), SW6.2
unnamed: D7.2 (A), SW7.2
unnamed: D8.2 (A), SW8.2
unnamed: D9.2 (A), SW9.2
unnamed: D10.2 (A), SW10.2
unnamed: D11.2 (A), SW11.2
unnamed: D12.2 (A), SW12.2
unnamed: D13.2 (A), SW13.2
unnamed: D14.2 (A), SW14.2
unnamed: D15.2 (A), SW15.2
unnamed: D16.2 (A), SW16.2
unnamed: D17.2 (A), SW17.2
unnamed: D18.2 (A), SW18.2
unnamed: D19.2 (A), SW19.2
unnamed: D20.2 (A), SW20.2
unnamed: D21.2 (A), SW21.2
